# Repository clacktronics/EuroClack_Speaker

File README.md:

# Clacktronics Mini-Speaker Kit

This project is a simple audio monitor module for your Eurorack. It consists of a speaker driver mounted onto an FR4 panel with an amplifier board. Much like the EDP Wasp or the Arp 2600, It will not be the most high definition speaker, especially lacking at the low end, but it is handy for when you may not be able to access your monitors or if you are using a small portable system.

As a kit it is designed to be simple and fast to assemble, so ideal for beginners. There are only a handful of components to solder so should give fast gratification and troubleshooting should be simple. The speaker is exactly 30.5mm wide which means it just fits into the 6HP (30mm) panel width.

* Width: 6HP
* Height: 3U
* Depth: 50mm
* Current draw idle: 5mA(+12V) 0mA(-12V) 0mA(5V)
* Current draw Active: 80mA(+12V) 0mA(-12V) 0mA(5V) (driven with 10Vpp square wave at 500kHz)

More information at [clacktronics.co.uk/euroclack](http://clacktronics.co.uk/euroclack)

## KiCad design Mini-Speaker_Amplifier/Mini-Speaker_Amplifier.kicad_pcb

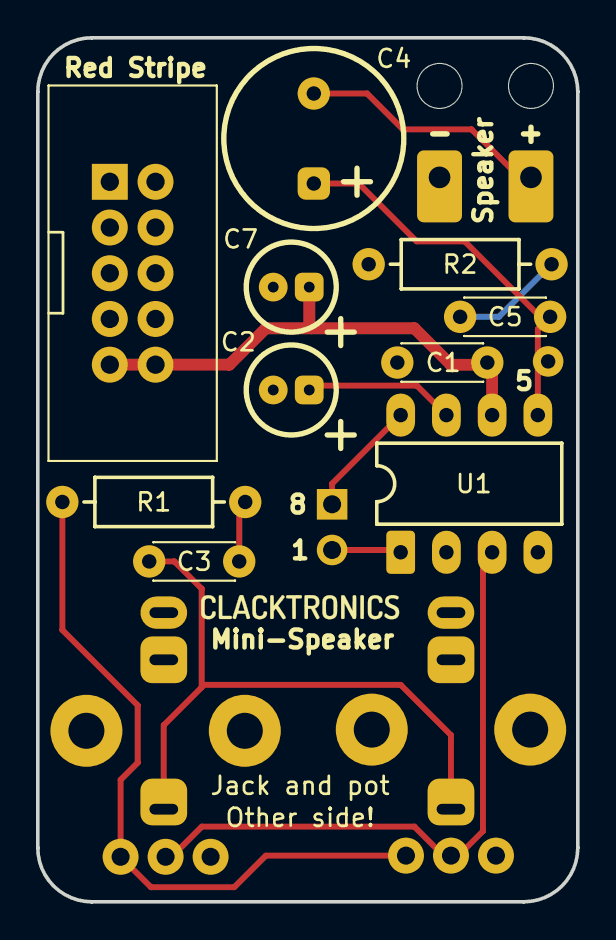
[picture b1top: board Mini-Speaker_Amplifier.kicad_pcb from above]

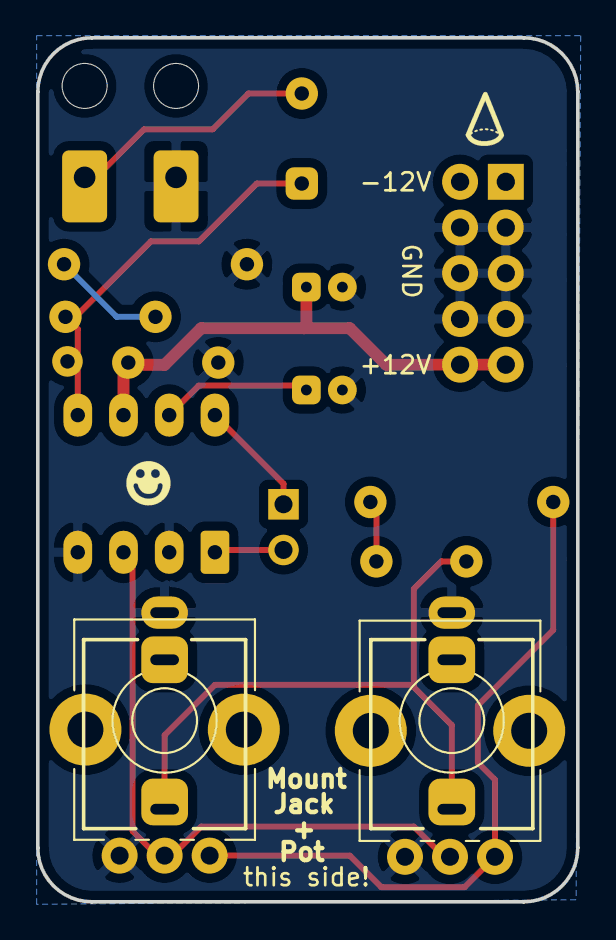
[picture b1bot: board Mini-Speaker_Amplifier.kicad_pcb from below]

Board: 2 copper layers, 30.0 x 48.0 mm, 16 parts (4 on the bottom side), 12 nets.

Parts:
C1, C3, C5: 100nF; C_TH_Disc_P5.00mm
C2, C7: 10μF; C_TH_Elec_5mm_P2mm
C4: 1000μF; C_TH_Elec_10mm_P5mm
J1, J1#2: AudioJack2; PJ398SM
J2: Conn_02x05; IDC-Header_2x05_P2.54mm_Vertical
J3: Conn_01x02; PinHeader_1x02_P2.54mm_Vertical
LS1: Speaker; Conn_speaker_pads
R1: 470k; R_TH_Axial_250mw_P10.16mm_Horizontal
R2: 10; R_TH_Axial_250mw_P10.16mm_Horizontal
RV1, RV1#2: 10k; POT_TH_Alps_RK09K_Single_Vertical
U1: LM386-4; DIP-8_W7.62mm

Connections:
+12V: C1.1, C7.1, J2.9, J2.10, U1.6
GND: C1.2, C2.2, C7.2, J1.S, J1#2.S, J2.3, J2.4, J2.5, J2.6, J2.7, J2.8, LS1.2, R2.1, RV1.3, RV1#2.3, U1.2, U1.4
unnamed: C2.1, U1.7
unnamed: C3.1, R1.2
unnamed: C3.2, J1.T, J1#2.T
unnamed: C4.1, C5.1, U1.5
unnamed: C4.2, LS1.1
unnamed: C5.2, R2.2
unnamed: J3.1, U1.8
unnamed: J3.2, U1.1
unnamed: R1.1, RV1.1, RV1#2.1
unnamed: RV1.2, RV1#2.2, U1.3

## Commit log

2019-09-23 Initial
2019-09-23 Added readme information
2019-09-23 Added image
2019-09-23 URL wrong
